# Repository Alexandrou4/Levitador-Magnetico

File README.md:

<h1 align="center"> **LEVITADOR MAGNÉTICO** </h1>

<h2> Nuestro proyecto, un levitador magnético por repulsión es un dispositivo que utiliza la fuerza de campos magnéticos para suspender un objeto en el aire sin contacto físico. </h2>

<h2> En este utilizamos los principios de electromagnetismo y corrientes eléctricas, PWM (Pulse Width Modulation/Modulación por Ancho de Pulso) y PID (Proporcional-Integral-Derivativo) como un sistema de control para regular constantemente la tensión media inducida en un electroimán en tiempo real y un circuito de potencia que nos permite tener la suficiente alimentación para el bobinado. </h2>

<h2> En este repositorio de Github se encuentran varios directorios como documentación, archivos del firmware, hardware y del sitio web para el facil acceso del lector, con una breve exlicación de los contenidos de cada dirección </h2>

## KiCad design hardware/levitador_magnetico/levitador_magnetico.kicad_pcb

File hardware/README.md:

<h1 align="center"> HARDWARE </h1>

<h2> Se encuentra una gran parte de los archivos del proyecto en este directorio</h2>

<h2> Se incluyen:</h2>

<h3> -Esquemático</h3>
<h3> -PCB</h3>
<h3> -Gerber</h3>
<h3> -Simbolo RP2040-Zero</h3>
<h3> -Footprint RP2040-Zero</h3>

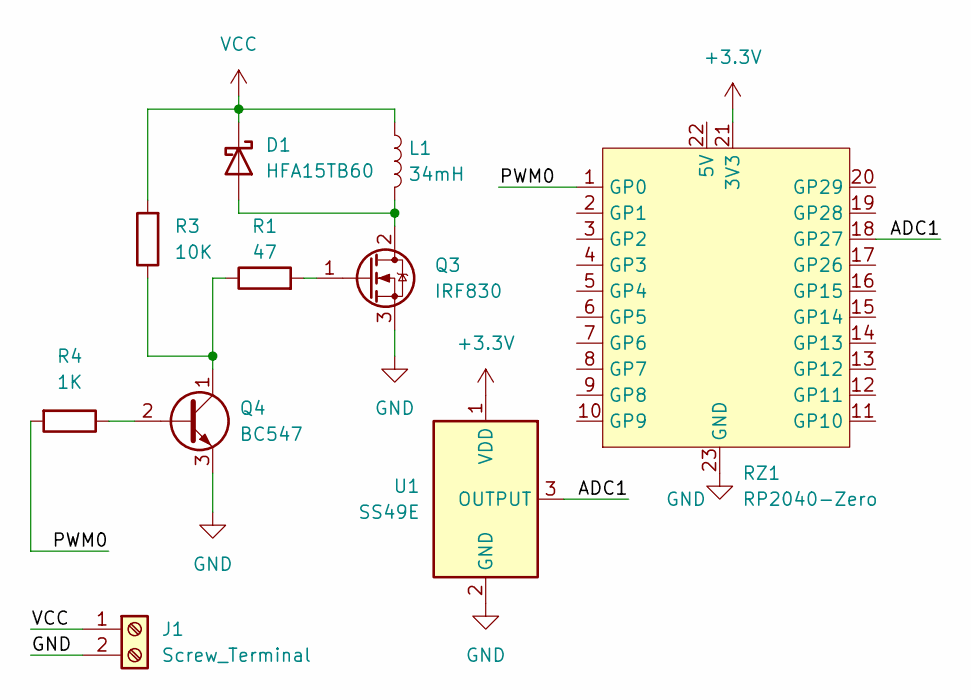
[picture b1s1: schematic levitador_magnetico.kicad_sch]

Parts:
D1: HFA15TB60; D_DO-41_SOD81_P10.16mm_Horizontal
J1: Screw_Terminal; TerminalBlock_bornier-2_P5.08mm
L1: 34mH; R_Axial_DIN0207_L6.3mm_D2.5mm_P7.62mm_Horizontal
Q3: IRF830; TO-220-3_Vertical
Q4: BC547; TO-92_Inline
R1: 47; L_Axial_L5.3mm_D2.2mm_P7.62mm_Horizontal_Vishay_IM-1
R3: 10K; L_Axial_L5.3mm_D2.2mm_P7.62mm_Horizontal_Vishay_IM-1
R4: 1K; L_Axial_L5.3mm_D2.2mm_P7.62mm_Horizontal_Vishay_IM-1
RZ1: RP2040-Zero
U1: SS49E; TO-92_Inline_Wide

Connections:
+3.3V: RZ1.21 (3V3), U1.1 (VDD)
/ADC1: RZ1.18 (GP27), U1.3 (OUTPUT)
/PWM0: R4.2, RZ1.1 (GP0)
GND: J1.2, Q3.3 (S), Q4.3 (E), RZ1.23 (GND), U1.2 (GND)
unnamed: D1.2 (A), L1.2, Q3.2 (D)
unnamed: Q3.1 (G), R1.2
unnamed: Q4.2 (B), R4.1
unnamed: Q4.1 (C), R1.1, R3.1
VCC: D1.1 (K), J1.1, L1.1, R3.2

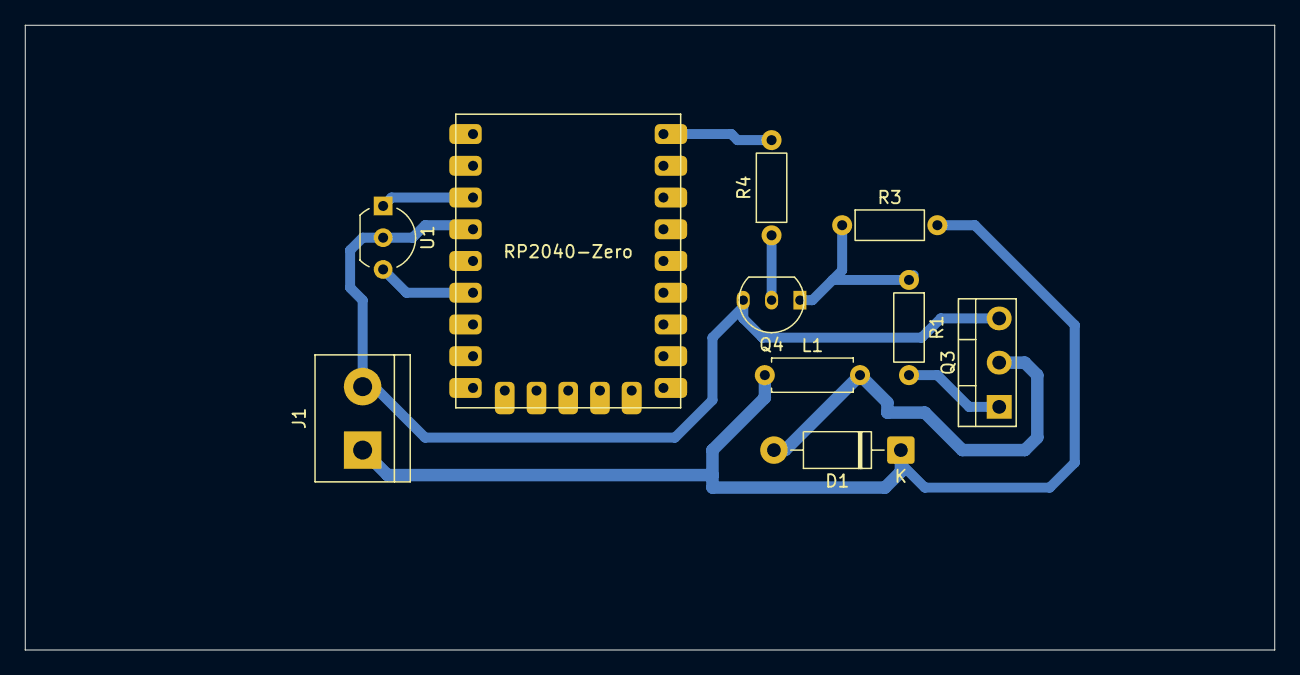
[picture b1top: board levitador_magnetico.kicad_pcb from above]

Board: 2 copper layers, 100.0 x 50.0 mm, 10 parts (0 on the bottom side), 9 nets.

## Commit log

2025-11-28 Create firmware
    .
2025-11-28 Create placeholder
2025-11-28 Cree un README
2025-11-28 Add README.md file
2025-11-28 Add README.md file to firmware directory
2025-11-28 Add project title and description to README
    Added project title and introductory text.
2025-11-28 Enhance README with project overview and details
    Added project description and repository details.
2025-11-28 Update headings in README.md for consistency
2025-11-28 Update README with website title and image
2025-11-28 Fix typo in README documentation description
2025-11-28 Fix typo in README.md regarding directories
